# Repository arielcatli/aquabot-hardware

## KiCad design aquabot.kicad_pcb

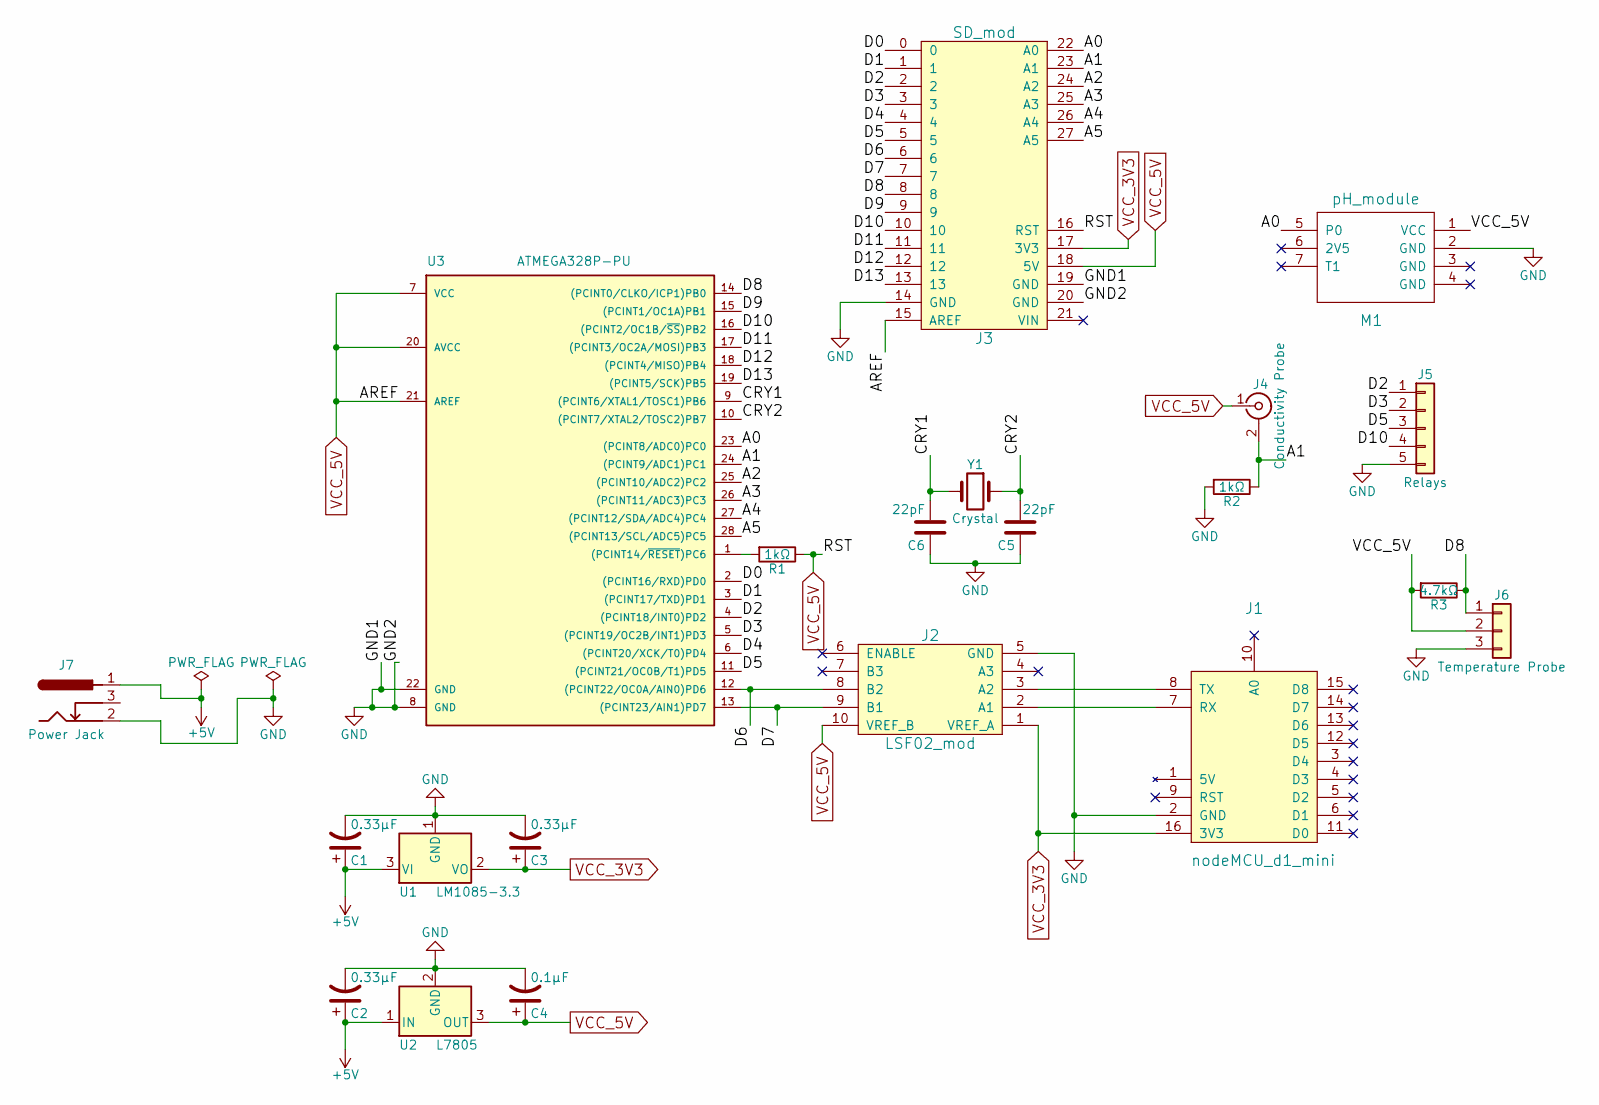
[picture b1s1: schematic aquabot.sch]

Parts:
C1, C2, C3: 0.33μF; CP_Radial_D8.0mm_P3.80mm
C4: 0.1μF; CP_Radial_D8.0mm_P3.80mm
C5, C6: 22pF; C_Disc_D3.4mm_W2.1mm_P2.50mm
J1: nodeMCU_d1_mini; NODEMCU_MODULE
J2: LSF02_mod; LSF02_MODULE
J3: SD_mod; SD_CARD_MODULE
J4: Conductivity Probe; BNC_Socket_TYCO-AMP_LargePads
J5: Relays; Socket_Strip_Straight_1x05_Pitch2.54mm
J6: Temperature Probe; Socket_Strip_Straight_1x03_Pitch2.54mm
J7: Power Jack; BARREL_JACK
M1: pH_module; pH_MODULE
R1, R2: 1kΩ; R_Axial_DIN0207_L6.3mm_D2.5mm_P7.62mm_Horizontal
R3: 4.7kΩ; R_Axial_DIN0207_L6.3mm_D2.5mm_P7.62mm_Horizontal
U1: LM1085-3.3; TO-220-3_Vertical
U2: L7805; TO-220-3_Vertical
U3: ATMEGA328P-PU; DIP-28_W7.62mm
Y1: Crystal; Crystal_HC49-4H_Vertical

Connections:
+5V: C1.1, C2.1, J7.1, U1.3 (VI), U2.1 (IN)
/A0: J3.22 (A0), M1.5 (P0), U3.23 ((PCINT8/ADC0)PC0)
/A1: J3.23 (A1), J4.2 (Ext), R2.1, U3.24 ((PCINT9/ADC1)PC1)
/A2: J3.24 (A2), U3.25 ((PCINT10/ADC2)PC2)
/A3: J3.25 (A3), U3.26 ((PCINT11/ADC3)PC3)
/A4: J3.26 (A4), U3.27 ((PCINT12/SDA/ADC4)PC4)
/A5: J3.27 (A5), U3.28 ((PCINT13/SCL/ADC5)PC5)
/CRY1: C6.2, U3.9 ((PCINT6/XTAL1/TOSC1)PB6), Y1.2
/CRY2: C5.2, U3.10 ((PCINT7/XTAL2/TOSC2)PB7), Y1.1
/D0: J3.0, U3.2 ((PCINT16/RXD)PD0)
/D1: J3.1, U3.3 ((PCINT17/TXD)PD1)
/D2: J3.2, J5.1, U3.4 ((PCINT18/INT0)PD2)
/D3: J3.3, J5.2, U3.5 ((PCINT19/OC2B/INT1)PD3)
/D4: J3.4, U3.6 ((PCINT20/XCK/T0)PD4)
/D5: J3.5, J5.3, U3.11 ((PCINT21/OC0B/T1)PD5)
/D6: J2.8 (B2), J3.6, U3.12 ((PCINT22/OC0A/AIN0)PD6)
/D7: J2.9 (B1), J3.7, U3.13 ((PCINT23/AIN1)PD7)
/D8: J3.8, J6.1, R3.1, U3.14 ((PCINT0/CLKO/ICP1)PB0)
/D9: J3.9, U3.15 ((PCINT1/OC1A)PB1)
/D10: J3.10, J5.4, U3.16 ((PCINT2/OC1B/~SS~)PB2)
/D11: J3.11, U3.17 ((PCINT3/OC2A/MOSI)PB3)
/D12: J3.12, U3.18 ((PCINT4/MISO)PB4)
/D13: J3.13, U3.19 ((PCINT5/SCK)PB5)
GND: C1.2, C2.2, C3.2, C4.2, C5.1, C6.1, J1.2 (GND), J2.5 (GND), J3.14 (GND), J3.19 (GND), J3.20 (GND), J5.5, J6.3, J7.2, M1.2 (GND), R2.2, U1.1 (GND), U2.2 (GND), U3.8 (GND), U3.22 (GND)
unnamed: J1.7 (RX), J2.2 (A1)
unnamed: J1.8 (TX), J2.3 (A2)
unnamed: R1.2, U3.1 ((PCINT14/~RESET~)PC6)
VCC_3V3: C3.1, J1.16 (3V3), J2.1 (VREF_A), J3.17 (3V3), U1.2 (VO)
VCC_5V: C4.1, J2.10 (VREF_B), J3.15 (AREF), J3.16 (RST), J3.18 (5V), J4.1 (In), J6.2, M1.1 (VCC), R1.1, R3.2, U2.3 (OUT), U3.7 (VCC), U3.20 (AVCC), U3.21 (AREF)

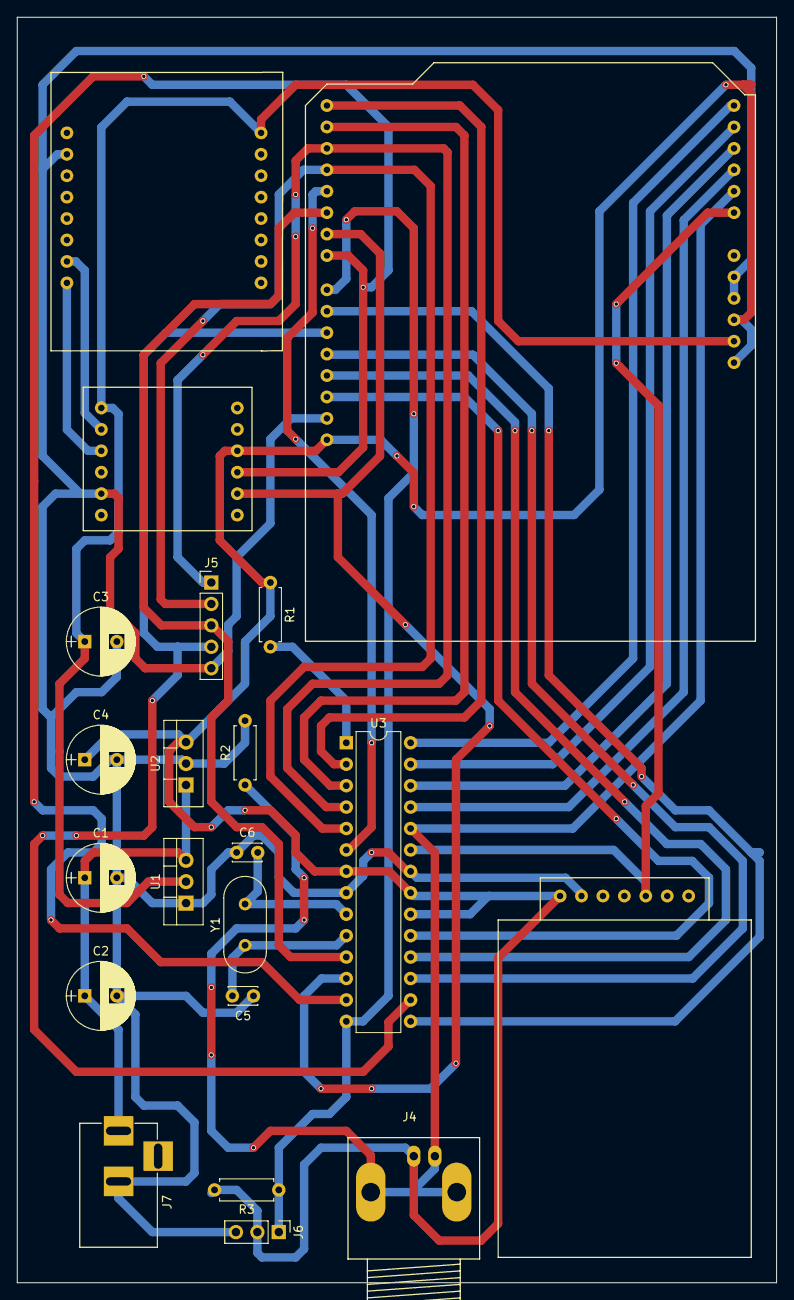
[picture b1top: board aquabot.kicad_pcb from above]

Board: 2 copper layers, 90.0 x 150.0 mm, 21 parts (0 on the bottom side), 29 nets.

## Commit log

2018-04-08 :octocat: Added .gitattributes & .gitignore files
